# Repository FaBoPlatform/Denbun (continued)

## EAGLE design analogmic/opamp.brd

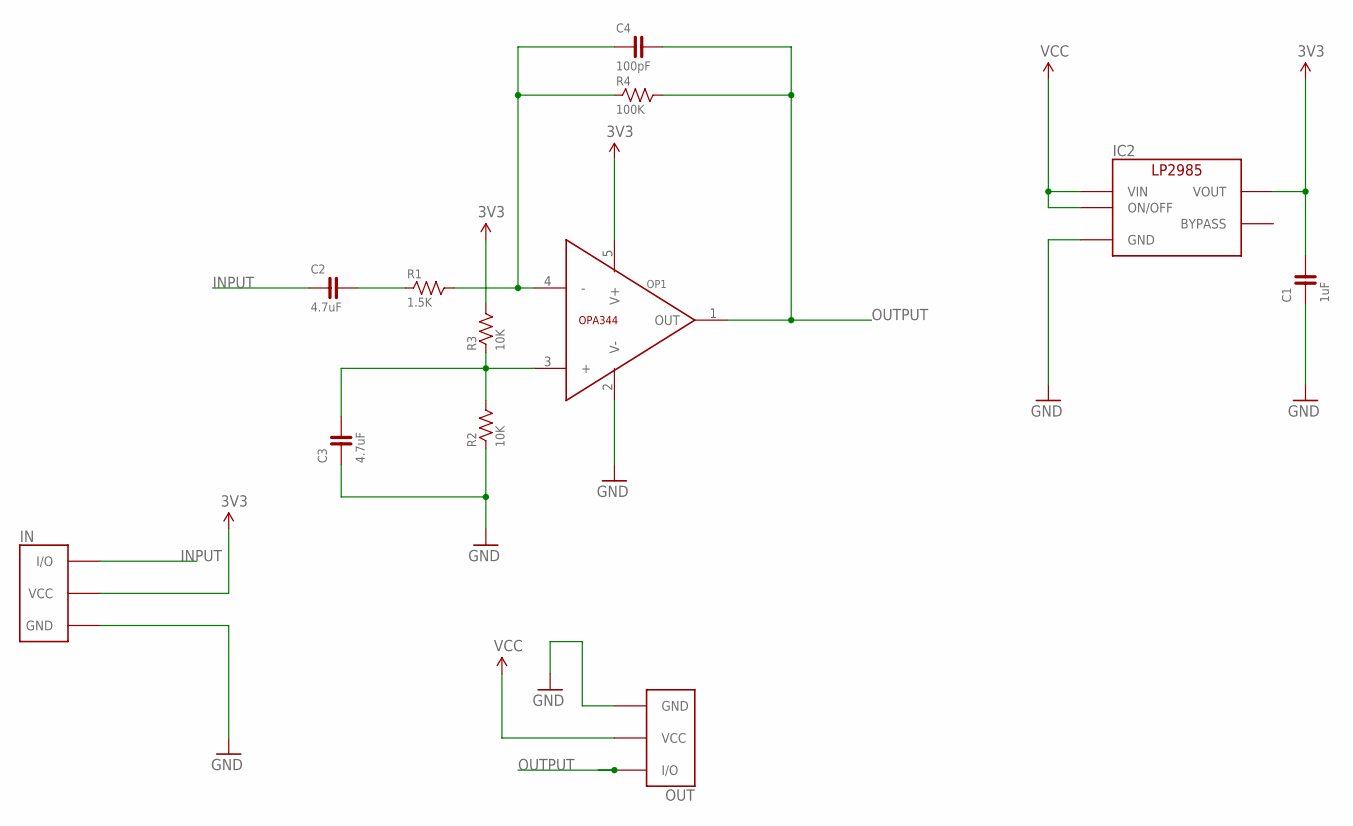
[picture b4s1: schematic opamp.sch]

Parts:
C1: 1uF; 0603
C2, C3: 4.7uF; 0603
C4: 100pF; 0603
IC2: LP2985-33DBV; SOT-23-5
IN: FABO_BRICK_3PIN-S03B-PASK-2; FABO_BRICK_3PIN_S03B-PASK-2
OP1: OPA344; SOT23-5
OUT: FABO_BRICK_3PIN-S03B-PASK-2; FABO_BRICK_3PIN_S03B-PASK-2
R1: 1.5K; 0603
R2, R3: 10K; 0603
R4: 100K; 0603

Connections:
3V3: C1.2, IC2.5 (VOUT), IN.VCC, OP1.5 (V+), R3.2
GND: C1.1, C3.1, IC2.2 (GND), IN.GND, OP1.2 (V-), OUT.GND, R2.1
INPUT: C2.1, IN.I/O
unnamed: C2.2, R1.1
unnamed: C3.2, OP1.3 (+), R2.2, R3.1
unnamed: C4.1, OP1.4 (-), R1.2, R4.1
OUTPUT: C4.2, OP1.1 (OUT), OUT.I/O, R4.2
VCC: IC2.1 (VIN), IC2.3 (ON/OFF), OUT.VCC

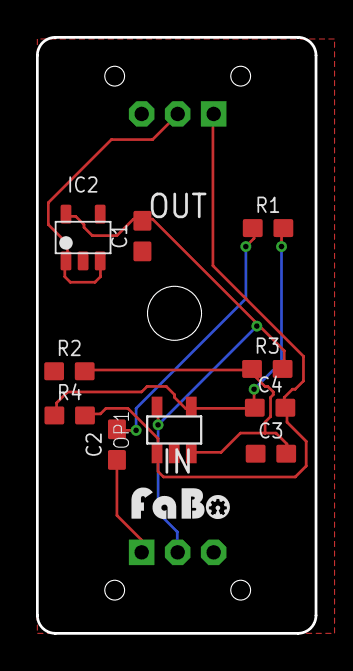
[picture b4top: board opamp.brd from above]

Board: 2 copper layers, 15.5 x 33.1 mm, 13 parts (0 on the bottom side), 8 nets.

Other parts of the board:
U$2: LOGO_FABO_S

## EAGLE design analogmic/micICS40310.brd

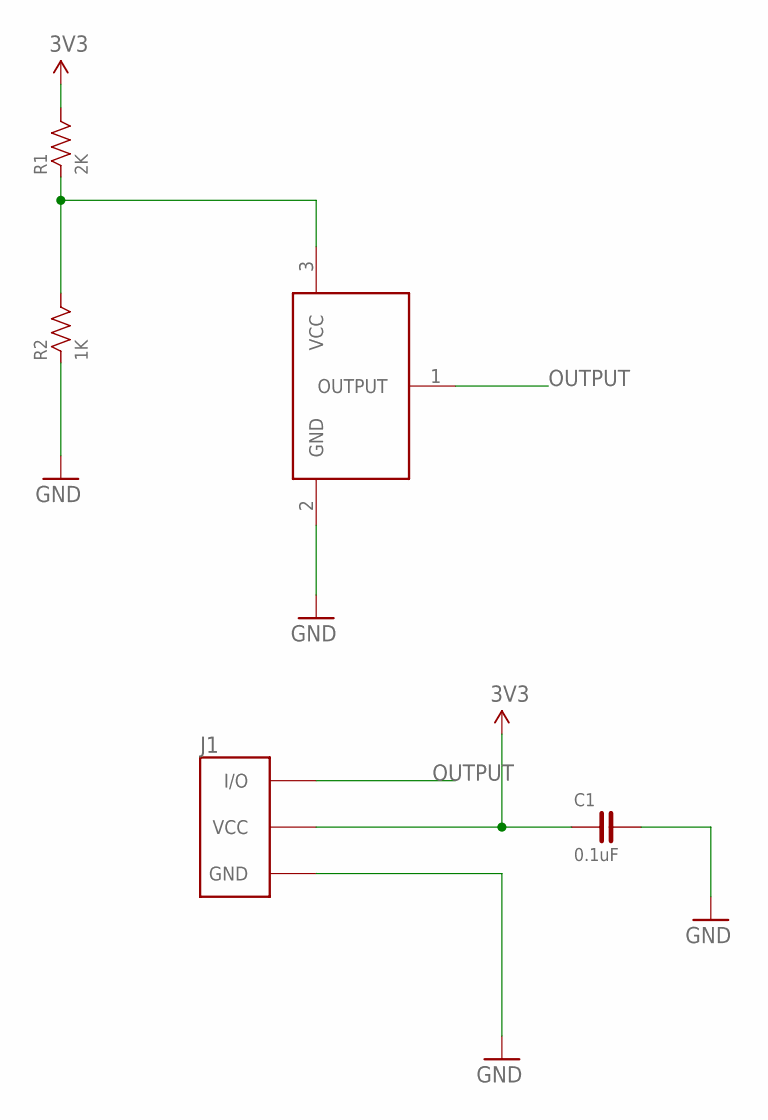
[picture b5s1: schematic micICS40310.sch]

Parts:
C1: 0.1uF; 0603
ICS40310: ANALOG-MICICS40310; ICS40310
J1: FABO_BRICK_3PIN-03B-PASK-1_NAME_BOTTOM; FABO_BRICK_3PIN_B03B-PASK-1_NAME_BOTTOM
R1: 2K; 0603
R2: 1K; 0603

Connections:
3V3: C1.1, J1.VCC, R1.2
GND: C1.2, ICS40310.2 (GND), J1.GND, R2.1
unnamed: ICS40310.3 (VCC), R1.1, R2.2
OUTPUT: ICS40310.1 (OUTPUT), J1.I/O

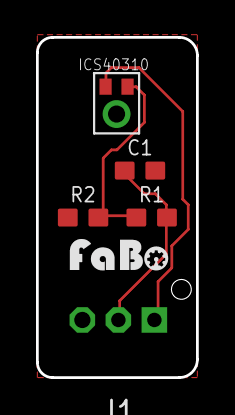
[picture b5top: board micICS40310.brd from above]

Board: 2 copper layers, 8.9 x 18.9 mm, 6 parts (0 on the bottom side), 4 nets.

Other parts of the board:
U$2: LOGO_FABO_S

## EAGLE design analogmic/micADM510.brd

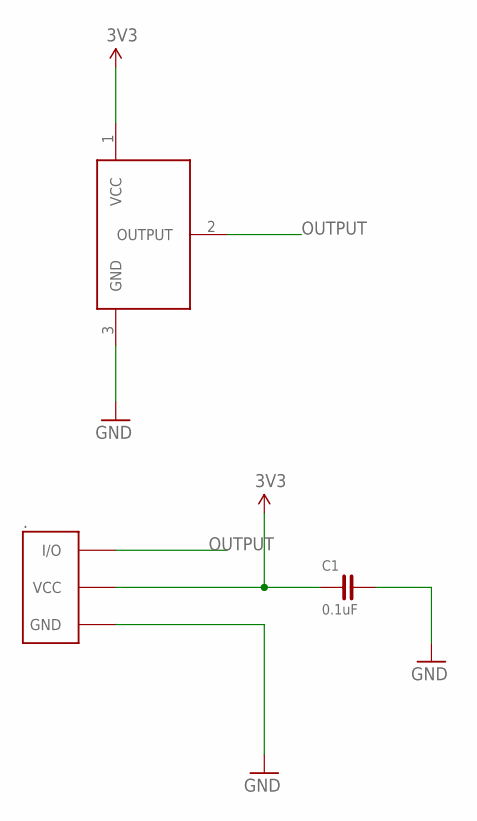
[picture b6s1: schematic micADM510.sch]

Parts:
.: FABO_BRICK_3PIN-S03B-PASK-2; FABO_BRICK_3PIN_S03B-PASK-2
ADM510: ANALOG-MICADMP510; INVERSENSE-ADMP510
C1: 0.1uF; 0603

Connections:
3V3: ..VCC, ADM510.1 (VCC), C1.1
GND: ..GND, ADM510.3 (GND), C1.2
OUTPUT: ..I/O, ADM510.2 (OUTPUT)

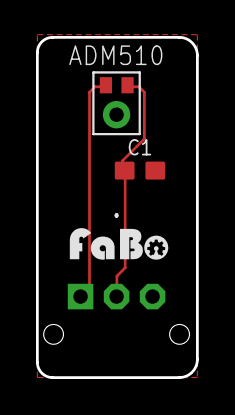
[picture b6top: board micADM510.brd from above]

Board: 2 copper layers, 8.9 x 18.9 mm, 4 parts (0 on the bottom side), 3 nets.

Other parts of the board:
U$2: LOGO_FABO_S

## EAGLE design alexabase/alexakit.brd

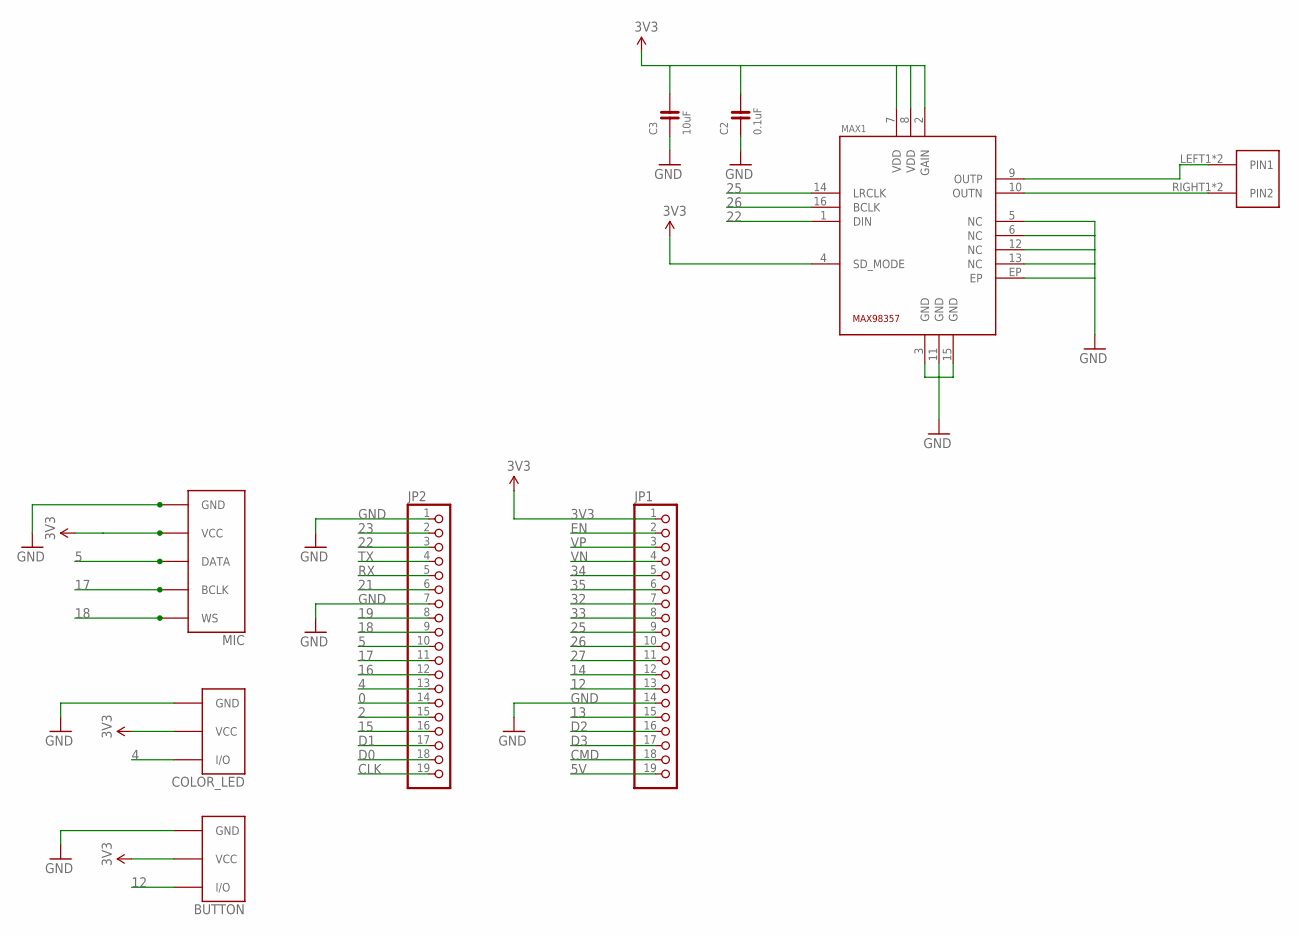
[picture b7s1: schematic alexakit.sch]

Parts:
BUTTON: BUTTON; FABO_BRICK_3PIN_B03B-PASK-1_NAME_BOTTOM
C2: 0.1uF; 0603
C3: 10uF; 0603
COLOR_LED: FABO_BRICK_3PIN-03B-PASK-1_NAME_BOTTOM; FABO_BRICK_3PIN_B03B-PASK-1_NAME_BOTTOM
JP1, JP2: PINHD-1X19; 1X19
MAX1: MA-MAX98357; MAXIM-MAX98357
MIC: FABO_BRICK_I2STOP; FABO_BRICK_I2S_B05B-PARK-1
U$4: ML-1400-S1

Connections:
0: JP2.14
2: JP2.15
3V3: BUTTON.VCC, C2.2, C3.2, COLOR_LED.VCC, JP1.1, MAX1.2 (GAIN), MAX1.4 (SD_MODE), MAX1.7 (VDD), MAX1.8 (VDD), MIC.VCC
4: COLOR_LED.I/O, JP2.13
5: JP2.10, MIC.DATA
5V: JP1.19
12: BUTTON.I/O, JP1.13
13: JP1.15
14: JP1.12
15: JP2.16
16: JP2.12
17: JP2.11, MIC.BCLK
18: JP2.9, MIC.WS
19: JP2.8
21: JP2.6
22: JP2.3, MAX1.1 (DIN)
23: JP2.2
25: JP1.9, MAX1.14 (LRCLK)
26: JP1.10, MAX1.16 (BCLK)
27: JP1.11
32: JP1.7
33: JP1.8
34: JP1.5
35: JP1.6
CLK: JP2.19
CMD: JP1.18
D0: JP2.18
D1: JP2.17
D2: JP1.16
D3: JP1.17
EN: JP1.2
GND: BUTTON.GND, C2.1, C3.1, COLOR_LED.GND, JP1.14, JP2.1, JP2.7, MAX1.3 (GND), MAX1.5 (NC), MAX1.6 (NC), MAX1.11 (GND), MAX1.12 (NC), MAX1.13 (NC), MAX1.15 (GND), MAX1.EP, MIC.GND
unnamed: MAX1.10 (OUTN), U$4.RIGHT1 (PIN2), U$4.RIGHT2 (PIN2)
unnamed: MAX1.9 (OUTP), U$4.LEFT1 (PIN1), U$4.LEFT2 (PIN1)
RX: JP2.5
TX: JP2.4
VN: JP1.4
VP: JP1.3

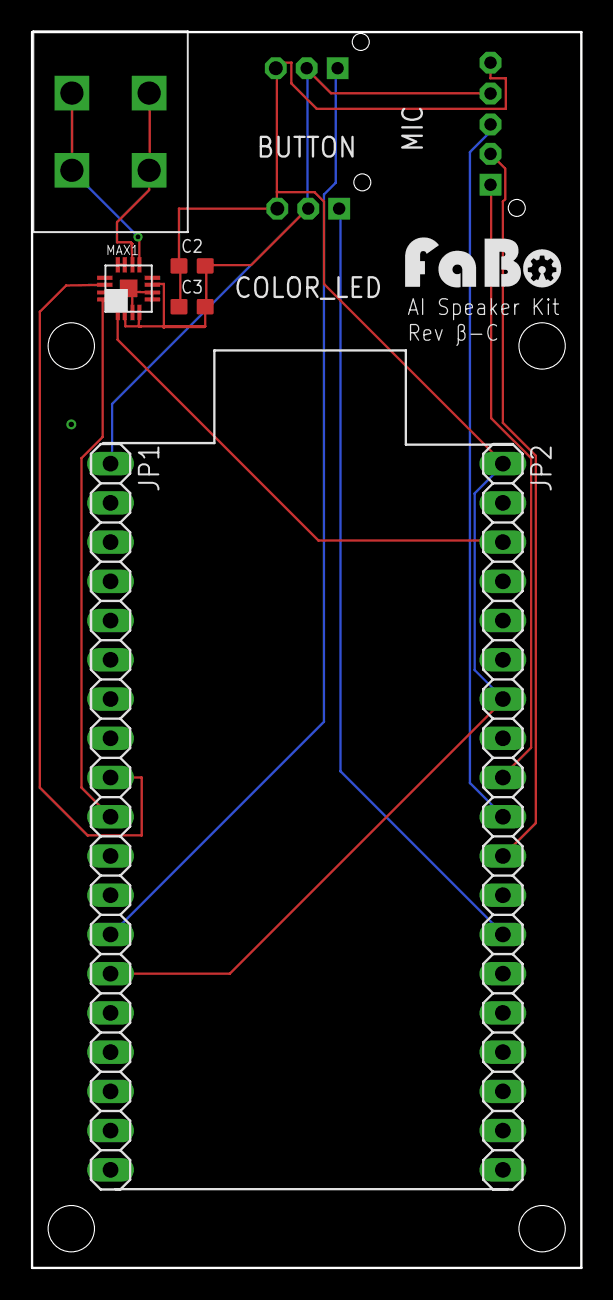
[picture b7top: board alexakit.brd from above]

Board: 2 copper layers, 35.6 x 80.0 mm, 10 parts (0 on the bottom side), 12 nets.

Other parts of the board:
U$2: LOGO_FABO_MS

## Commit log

2018-11-01 Initial commit.
2018-11-01 Add array mic.
2018-11-16 Update alexakit.
2018-11-16 Add analog mic.
2018-11-18 Change TX and RX.
2018-11-25 Update opamp.
2018-12-05 Add motor.
2018-12-05 Update.
2018-12-06 Add again.
2018-12-10 devボード見直し
2018-12-11 Update motor.
2019-01-07 fix route
2019-03-06 SensorHub Addtion.
    ESP32 WROOVER B
    Sensor Hub
2019-03-07 SensorHubRev4Update
    Addtion i2C EMI Filter Add
2019-03-07 Angle fixture
2019-03-07 SensorHub
    Botton position change.
2019-03-13 Revsionup to 6
2019-03-14 no message
2019-03-15 New Revision7 PULL UP VOLTAGE SELECT
    PULL UP VOLTAGE ENABLE
